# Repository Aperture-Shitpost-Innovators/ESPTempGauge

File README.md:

[![Contributors][contributors-shield]][contributors-url]
[![Forks][forks-shield]][forks-url]
[![Stargazers][stars-shield]][stars-url]
[![Issues][issues-shield]][issues-url]
[![project_license][license-shield]][license-url]

<!-- PROJECT LOGO -->
<br />
<div align="center">

<h3 align="center">Aperture Shitpost Innovators Highly Modular Engine Lubrication Liquid Thermal Reading Apparatus</h3>

  <p align="center">
    ESP32-WROOM32 based oil temperature gauge with noise filtering, smooth movement and OTA updates.
    <br />
    <br />
    <br />
    <a href="https://github.com/Aperture-Shitpost-Innovators/ESPTempGauge/issues/new?labels=bug&template=bug-report---.md">Report Bug</a>
    &middot;
    <a href="https://github.com/Aperture-Shitpost-Innovators/ESPTempGauge/issues/new?labels=enhancement&template=feature-request---.md">Request Feature</a>
  </p>
</div>

<!-- TABLE OF CONTENTS -->
<details>
  <summary>Table of Contents</summary>
  <ol>
    <li>
      <a href="#about-the-project">About The Project</a>
      <ul>
        <li><a href="#built-with">Built With</a></li>
      </ul>
    </li>
    <li>
      <a href="#getting-started">Getting Started</a>
      <ul>
        <li><a href="#Hardware">Hardware</a></li>
        <ul>
          <li><a href="#parts-list">Parts list</a></li>
          <li><a href="#Harness">Harness</a></li>
          <li><a href="#Adapter">Adapter</a></li>
        </ul>
        <li><a href="#Software">Software</a></li>
        <ul>
          <li><a href="#prerequisites">Prerequisites</a></li>
          <li><a href="#installation">Installation</a></li>
        </ul>
      </ul>
    </li>
    <li><a href="#roadmap">Roadmap</a></li>
    <li><a href="#contributing">Contributing</a></li>
    <li><a href="#license">License</a></li>
    <li><a href="#contact">Contact</a></li>
    <li><a href="#acknowledgments">Acknowledgments</a></li>
  </ol>
</details>

<!-- ABOUT THE PROJECT -->
## About The Project

This is a customizable oil temperature gauge software repository. The default style was designed after the 9'th generation Honda Civic gauge cluster. This source code was designed to be compilable and uploadable onto an ESP32-WROOM32 out of the box using Visual Studio Code and PlatformIO.

<p align="right">(<a href="#readme-top">back to top</a>)</p>

### Built With

* 
* 
* 
* 
  
<p align="right">(<a href="#readme-top">back to top</a>)</p>

<!-- GETTING STARTED -->
## Getting Started
Here are instructions on how to get the project up and running locally

### Hardware
#### Parts list
* ESP32-WROOM-32E
* GC9A01A based 1.28" round display (Prefferably the slim waveshare version, the others have a big PCB and will not fit for the Civic's dash)
* NTC Oil temperature of your choice
* USB - UART programmer, prefferably an FTDI FT232RL based one
* Custom ordered or manufactured PCB.
* Miscellanious parts listed below.

NOTE: The non-PSRAM models cant fit the full screen into memory and thus to maintain compatibility, it will show a black bar on the bottom of the screen. It's not visible in normal mode, but will show up during an alarm.
This is a hardware limitation.

You will need to either manufacture or order a custom PCB for this project, either will work. I have provided a kicad project in the `hardware` folder if you wish to order one or modify my design.

#### Harness
Wire together a harness according to the provided schematic. Please keep the power and NTC wires above 0.75mm2 to prevent excessive voltage drops.

#### Adapter

For this project, I used an oil filter sandwich plate with 1/8 NPT sensor ports. For the purposes of fitting it into an R18 block, I had to modify mine to fit, so I blocked off it's 2 ports leaving one free, grinded down the aluminium block and torqued down the sensor. To avoid leaks, I used a medium strength oil resistant thread-locker on all NPT threads. While it should seal well about 2h after installing the thread-locker, you should allow 24h to ensure a full cure. 

- **Do not apply threadlocker to the oil filter thread.**
- **Make sure to install the sandwich plate in the correct orientation to avoid serious oil leaks and possible engine damage**
- **Inspect the sandwich plate after installation to ensure no leaks**

 Modified plate            |  Fitted plate
:-------------------------:|:-------------------------:
 | 

### Software

### Prerequisites

This is an example of how to list things you need to use the software and how to install them.
* [Visual Studio Code](https://code.visualstudio.com/)
* [PlatformIO extension](https://platformio.org/install/ide?install=vscode)

### Installation
#### USB upload

1. Install prerequisites.
2. Clone the repo
   ```sh
   git clone https://github.com/Aperture-Shitpost-Innovators/ESPTempGauge.git
   ```
3. Do measurements of your sensor and input the Steinhart-Hart coefficients into the config variables.
4. Configure the OTA wifi name and password.
5. Connect your ESP32 board and wire in the screen and sensors.
6. In Visual Studio Code's PlatformIO tab, click "Upload".

#### OTA Updates (Firmware needs to be flashed once before and OTA updates enabled!)

1. Make your changes and build the project.
2. Navigate into `.pio/build` and find the `firmware.bin` file.
3. Make a hotspot matching the WiFi name and password that were set in `include/wifi_passes.h`.
4. Start the ESP32. If it connects successfully, it should show `UPDATE MODE` on the screen.
5. Connect to the WiFi using your laptop and navigate to the ESP32's web page. By default, it is [http://esp32.local](http://esp32.local).
6. Select your new `firmware.bin` file and click "Upload".
7. Once it finishes and you see the gauge restart, stop your hotspot and power cycle it.

<p align="right">(<a href="#readme-top">back to top</a>)</p>

<!-- ROADMAP -->
## Roadmap

- [x] Usable oil gauge
- [x] Proper documentation and instructions
- [ ] Refactored code
    - [ ] Easy to read code
    - [ ] Split into separate files
- [ ] Easily customizable user interface

See the [open issues](https://github.com/Aperture-Shitpost-Innovators/ESPTempGauge/issues) for a full list of proposed features (and known issues).

<p align="right">(<a href="#readme-top">back to top</a>)</p>

<!-- CONTRIBUTING -->
## Contributing

Contributions are what make the open source community such an amazing place to learn, inspire, and create. Any contributions you make are **greatly appreciated**.

If you have a suggestion that would make this better, please fork the repo and create a pull request. You can also simply open an issue with the tag "enhancement".
Don't forget to give the project a star! Thanks again!

1. Fork the Project
2. Create your Feature Branch (`git checkout -b feature/AmazingFeature`)
3. Commit your Changes (`git commit -m 'Add some AmazingFeature'`)
4. Push to the Branch (`git push origin feature/AmazingFeature`)
5. Open a Pull Request

<p align="right">(<a href="#readme-top">back to top</a>)</p>

### Top contributors:

<!-- LICENSE -->
## License

Distributed under the MIT license. See the `LICENSE` file for more information.

<p align="right">(<a href="#readme-top">back to top</a>)</p>

<!-- CONTACT -->
## Contact

Project Link: [https://github.com/Aperture-Shitpost-Innovators/ESPTempGauge](https://github.com/Aperture-Shitpost-Innovators/ESPTempGauge)

<p align="right">(<a href="#readme-top">back to top</a>)</p>

<!-- ACKNOWLEDGMENTS -->
## Acknowledgments

* [TFT_eSPI library](https://github.com/Bodmer/TFT_espi)
* [PNGdec library](https://github.com/bitbank2/PNGdec)
* [Simple Kalman Filter](https://github.com/denyssene/SimpleKalmanFilter)
* [This really cool README template](https://github.com/othneildrew/Best-README-Template)

<p align="right">(<a href="#readme-top">back to top</a>)</p>

<!-- MARKDOWN LINKS & IMAGES -->
<!-- https://www.markdownguide.org/basic-syntax/#reference-style-links -->
[contributors-shield]: https://img.shields.io/github/contributors/Aperture-Shitpost-Innovators/ESPTempGauge.svg?style=for-the-badge
[contributors-url]: https://github.com/Aperture-Shitpost-Innovators/ESPTempGauge/graphs/contributors
[forks-shield]: https://img.shields.io/github/forks/Aperture-Shitpost-Innovators/ESPTempGauge.svg?style=for-the-badge
[forks-url]: https://github.com/Aperture-Shitpost-Innovators/ESPTempGauge/network/members
[stars-shield]: https://img.shields.io/github/stars/Aperture-Shitpost-Innovators/ESPTempGauge.svg?style=for-the-badge
[stars-url]: https://github.com/Aperture-Shitpost-Innovators/ESPTempGauge/stargazers
[issues-shield]: https://img.shields.io/github/issues/Aperture-Shitpost-Innovators/ESPTempGauge.svg?style=for-the-badge
[issues-url]: https://github.com/Aperture-Shitpost-Innovators/ESPTempGauge/issues
[license-shield]: https://img.shields.io/github/license/Aperture-Shitpost-Innovators/ESPTempGauge.svg?style=for-the-badge
[license-url]: https://github.com/Aperture-Shitpost-Innovators/ESPTempGauge/blob/master/LICENSE
[linkedin-shield]: https://img.shields.io/badge/-LinkedIn-black.svg?style=for-the-badge&logo=linkedin&colorB=555
[linkedin-url]: https://linkedin.com/in/linkedin_username
[product-screenshot]: images/irl.png

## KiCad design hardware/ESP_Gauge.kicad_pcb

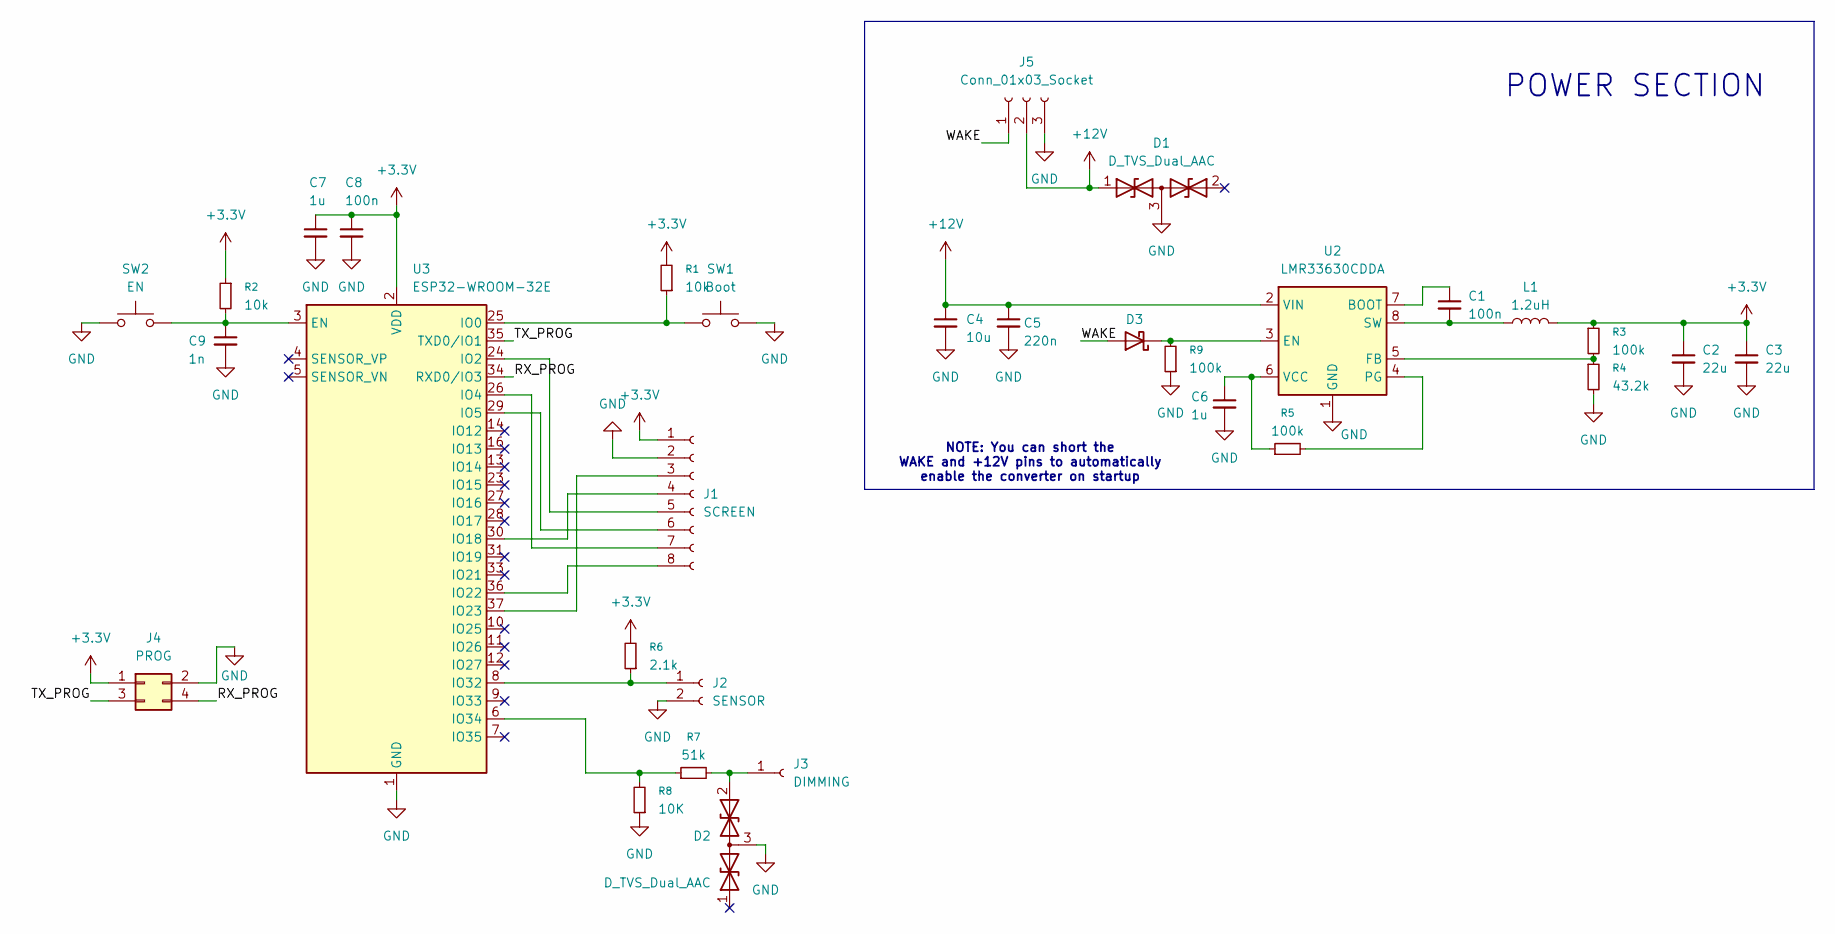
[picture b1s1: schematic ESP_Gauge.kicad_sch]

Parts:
C1, C8: 100n; C_0603_1608Metric_Pad1.08x0.95mm_HandSolder
C2, C3: 22u; C_0603_1608Metric_Pad1.08x0.95mm_HandSolder
C4: 10u; C_0603_1608Metric_Pad1.08x0.95mm_HandSolder
C5: 220n; C_0603_1608Metric_Pad1.08x0.95mm_HandSolder
C6, C7: 1u; C_0603_1608Metric_Pad1.08x0.95mm_HandSolder
C9: 1n; C_0603_1608Metric_Pad1.08x0.95mm_HandSolder
D1, D2: D_TVS_Dual_AAC; SOT-23-3
D3: D_Schottky; D_0603_1608Metric
J1: SCREEN; JST_XH_B8B-XH-AM_1x08_P2.50mm_Vertical
J2: SENSOR; SolderWire-0.75sqmm_1x02_P7mm_D1.25mm_OD3.5mm_Relief
J3: DIMMING; SolderWire-0.75sqmm_1x01_D1.25mm_OD3.5mm_Relief
J4: PROG; PinHeader_2x02_P2.54mm_Vertical
J5: Conn_01x03_Socket; SolderWire-0.75sqmm_1x03_P7mm_D1.25mm_OD3.5mm_Relief
L1: 1.2uH; L_1008_2520Metric_Pad1.43x2.20mm_HandSolder
R1, R2: 10k; R_0603_1608Metric_Pad0.98x0.95mm_HandSolder
R3, R5, R9: 100k; R_0603_1608Metric_Pad0.98x0.95mm_HandSolder
R4: 43.2k; R_0603_1608Metric_Pad0.98x0.95mm_HandSolder
R6: 2.1k; R_0603_1608Metric_Pad0.98x0.95mm_HandSolder
R7: 51k; R_0603_1608Metric_Pad0.98x0.95mm_HandSolder
R8: 10K; R_0603_1608Metric_Pad0.98x0.95mm_HandSolder
SW1: Boot; SW_PUSH_6mm_H5mm
SW2: EN; SW_PUSH_6mm_H5mm
U2: LMR33630CDDA; Texas_HSOP-8-1EP_3.9x4.9mm_P1.27mm_ThermalVias
U3: ESP32-WROOM-32E; ESP32-WROOM-32D

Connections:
+3.3V: C2.1, C3.1, C7.1, C8.1, J1.1, J4.1, L1.2, R1.2, R2.1, R3.1, R6.2, U3.2 (VDD)
+12V: C4.1, C5.1, D1.1 (A1), J5.2, U2.2 (VIN)
/RX_PROG: J4.4, U3.34 (RXD0/IO3)
/TX_PROG: J4.3, U3.35 (TXD0/IO1)
/WAKE: D3.2 (A), J5.1
GND: C2.2, C3.2, C4.2, C5.2, C6.2, C7.2, C8.2, C9.2, D1.3 (common), D2.3 (common), J1.2, J2.2, J4.2, J5.3, R4.2, R8.1, R9.1, SW1.2, SW2.2, U2.1 (GND), U2.9 (GND), U3.1 (GND), U3.15 (GND), U3.38 (GND), U3.39 (GND)
unnamed: D2.2 (A2), J3.1 (Pin_1_1), R7.2
unnamed: D3.1 (K), R9.2, U2.3 (EN)
unnamed: J1.3, U3.37 (IO23)
unnamed: J1.4, U3.30 (IO18)
unnamed: J1.5, U3.24 (IO2)
unnamed: J1.6, U3.29 (IO5)
unnamed: J1.7, U3.26 (IO4)
unnamed: J1.8, U3.36 (IO22)
unnamed: J2.1, R6.1, U3.8 (IO32)
unnamed: C1.1, U2.7 (BOOT)
unnamed: R3.2, R4.1, U2.5 (FB)
unnamed: R5.2, U2.4 (PG)
unnamed: C1.2, L1.1, U2.8 (SW)
unnamed: C6.1, R5.1, U2.6 (VCC)
unnamed: C9.1, R2.2, SW2.1, U3.3 (EN)
unnamed: R1.1, SW1.1, U3.25 (IO0)
unnamed: R7.1, R8.2, U3.6 (IO34)

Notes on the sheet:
NOTE: You can short the WAKE and +12V pins to automatically enable the converter on startup
POWER SECTION

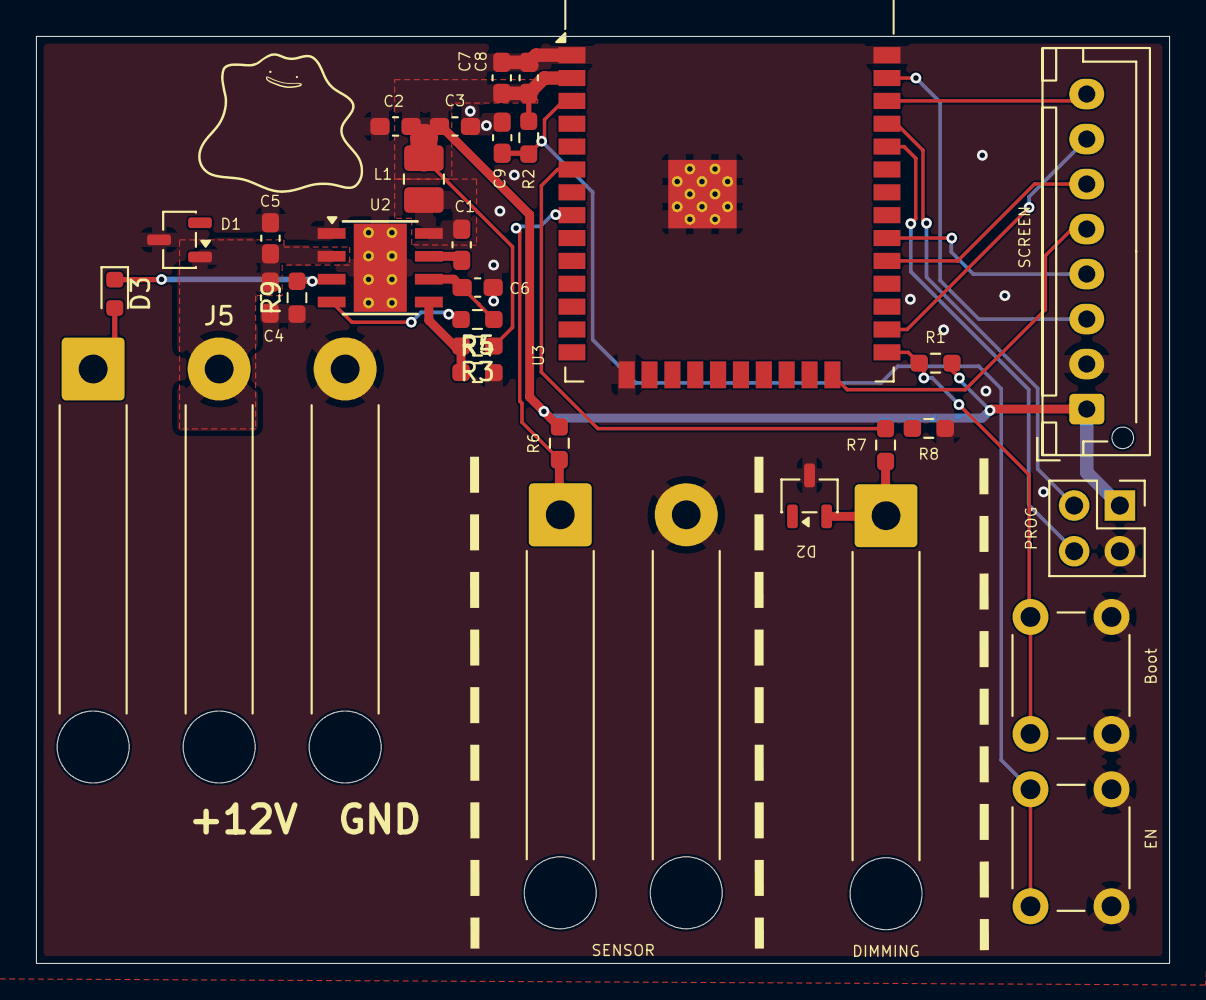
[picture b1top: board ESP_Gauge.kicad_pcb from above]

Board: 2 copper layers, 63.0 x 51.5 mm, 31 parts (0 on the bottom side), 23 nets.
